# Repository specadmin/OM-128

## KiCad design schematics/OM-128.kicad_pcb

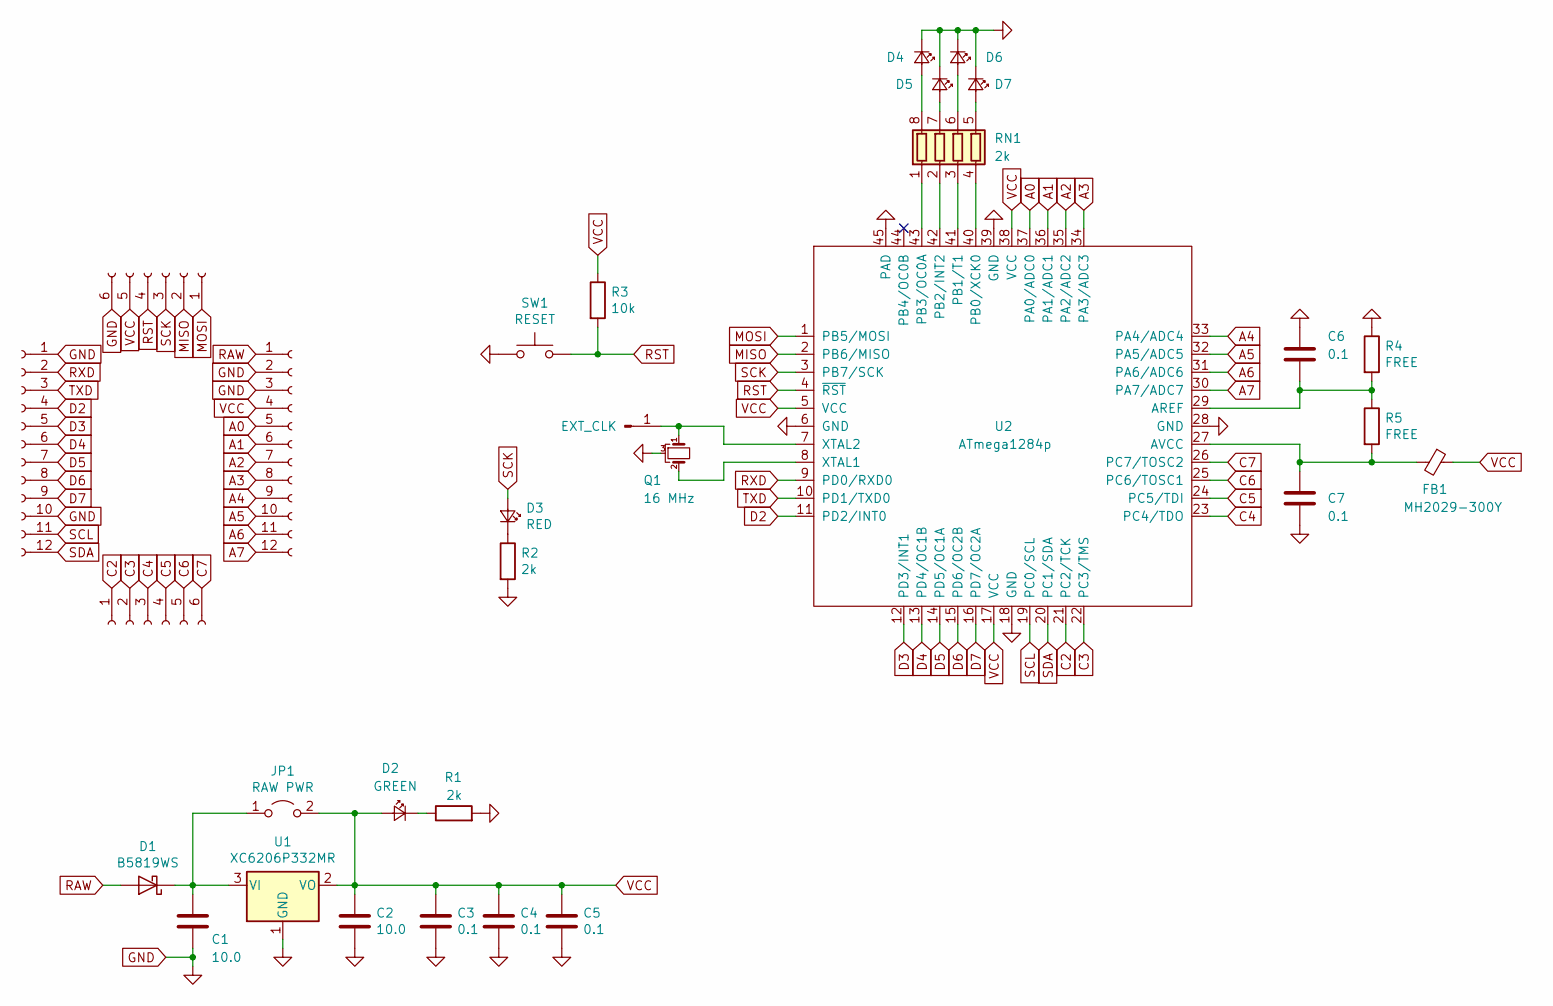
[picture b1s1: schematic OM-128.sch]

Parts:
C1, C2: 10.0; C_0603_1608Metric
C3, C4, C5, C6, C7: 0.1; C_0603_1608Metric
D1: B5819WS; D_SOD-323_HandSoldering
D2: GREEN; LED_0603_1608Metric
D3: RED; LED_0603_1608Metric
D4: B3; LED_0603_1608Metric
D5: B2; LED_0603_1608Metric
D6: B1; LED_0603_1608Metric
D7: B0; LED_0603_1608Metric
FB1: MH2029-300Y; L_0805_2012Metric
J1: LEFT; PinHeader_1x12_P2.54mm_Vertical
J2: TOP; PinHeader_1x06_P2.54mm_Vertical
J3: BOTTOM; PinHeader_1x06_P2.54mm_Vertical
J4: RIGHT; PinHeader_1x12_P2.54mm_Vertical
J5: EXT_CLK; TestPoint_Pad_1.0x1.0mm
JP1: RAW PWR; SolderJumper-2_P1.3mm_Open_RoundedPad1.0x1.5mm
Q1: 16 MHz; Murata_CSTCExxxxV_3213_crystal
R1, R2: 2k; R_0603_1608Metric
R3: 10k; R_0603_1608Metric
R4, R5: FREE; R_0603_1608Metric
RN1: 2k; R_Array_Concave_4x0402
SW1: RESET; SW_SPST_CK_RS282G05A3
U1: XC6206P332MR; SOT-23
U2: ATmega1284p; QFN-44-1EP_7x7mm_P0.5mm_EP5.2x5.2mm_ThermalVias

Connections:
A0: J4.5, U2.37 (PA0/ADC0)
A1: J4.6, U2.36 (PA1/ADC1)
A2: J4.7, U2.35 (PA2/ADC2)
A3: J4.8, U2.34 (PA3/ADC3)
A4: J4.9, U2.33 (PA4/ADC4)
A5: J4.10, U2.32 (PA5/ADC5)
A6: J4.11, U2.31 (PA6/ADC6)
A7: J4.12, U2.30 (PA7/ADC7)
C2: J3.1, U2.21 (PC2/TCK)
C3: J3.2, U2.22 (PC3/TMS)
C4: J3.3, U2.23 (PC4/TDO)
C5: J3.4, U2.24 (PC5/TDI)
C6: J3.5, U2.25 (PC6/TOSC1)
C7: J3.6, U2.26 (PC7/TOSC2)
D2: J1.4, U2.11 (PD2/INT0)
D3: J1.5, U2.12 (PD3/INT1)
D4: J1.6, U2.13 (PD4/OC1B)
D5: J1.7, U2.14 (PD5/OC1A)
D6: J1.8, U2.15 (PD6/OC2B)
D7: J1.9, U2.16 (PD7/OC2A)
GND: C1.2, C2.2, C3.2, C4.2, C5.2, C6.2, C7.1, D4.1 (K), D5.1 (K), D6.1 (K), D7.1 (K), J1.1, J1.10, J2.6, J4.2, J4.3, Q1.3, R1.2, R2.2, R4.1, SW1.1, U1.1 (GND), U2.6 (GND), U2.18 (GND), U2.28 (GND), U2.39 (GND), U2.45 (PAD)
MISO: J2.2, U2.2 (PB6/MISO)
MOSI: J2.1, U2.1 (PB5/MOSI)
unnamed: C1.1, D1.1 (K), JP1.1 (A), U1.3 (VI)
unnamed: C6.1, R4.2, R5.1, U2.29 (AREF)
unnamed: C7.2, FB1.2, R5.2, U2.27 (AVCC)
unnamed: D2.1 (K), R1.1
unnamed: D3.1 (K), R2.1
unnamed: D4.2 (A), RN1.8 (R1.2)
unnamed: D5.2 (A), RN1.7 (R2.2)
unnamed: D6.2 (A), RN1.6 (R3.2)
unnamed: D7.2 (A), RN1.5 (R4.2)
unnamed: J5.1, Q1.1, U2.7 (XTAL2)
unnamed: Q1.2, U2.8 (XTAL1)
unnamed: RN1.1 (R1.1), U2.43 (PB3/OC0A)
unnamed: RN1.2 (R2.1), U2.42 (PB2/INT2)
unnamed: RN1.3 (R3.1), U2.41 (PB1/T1)
unnamed: RN1.4 (R4.1), U2.40 (PB0/XCK0)
RAW: D1.2 (A), J4.1
RST: J2.4, R3.2, SW1.2, U2.4 (~RST)
RXD: J1.2, U2.9 (PD0/RXD0)
SCK: D3.2 (A), J2.3, U2.3 (PB7/SCK)
SCL: J1.11, U2.19 (PC0/SCL)
SDA: J1.12, U2.20 (PC1/SDA)
TXD: J1.3, U2.10 (PD1/TXD0)
VCC: C2.1, C3.1, C4.1, C5.1, D2.2 (A), FB1.1, J2.5, J4.4, JP1.2 (B), R3.1, U1.2 (VO), U2.5 (VCC), U2.17 (VCC), U2.38 (VCC)

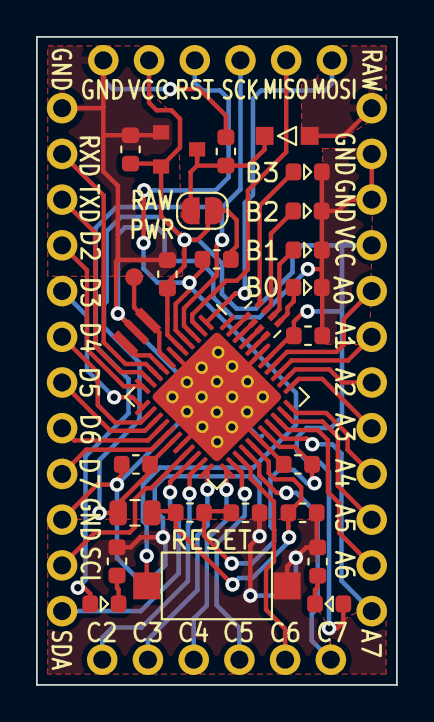
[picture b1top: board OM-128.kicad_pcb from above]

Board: 2 copper layers, 20.0 x 36.0 mm, 31 parts (0 on the bottom side), 46 nets.

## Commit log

2020-01-17 Readme changed
2020-01-17 Disable watchdog in a proper way
2020-01-17 Submodules added
2020-10-30 Обновлены версии библиотек
2020-11-22 Minor improvements
2021-02-21 Default firmware changes
2022-02-21 Rotate images
